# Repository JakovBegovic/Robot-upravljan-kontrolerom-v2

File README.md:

# Robot upravljan kontrolerom v2
[![CC BY-NC-SA 4.0][cc-by-nc-sa-shield]][cc-by-nc-sa]
<br>

Samostalan projekt studenta 2. godine diplomskog studija Jakova Begovića razvijen u svrhu učenja i razvijanja znanja. <br><br>
Koncipiran kao unaprjeđenje [projekta](https://github.com/JakovBegovic/Robot-upravljan-kontrolerom) razvijenog na 3. godini preddiplomskog studija. <br>
Uzima inspiraciju od prvotnog projekta i unaprjeđuje njegove značajke u svrhu povećane energetske učinkovitosti, korisničkog iskustva i funkcionalnosti.<br><br>

### Stanje razvoja dizajna za v2:
  - Razvijeni programski kodovi na prototipima električnih shema robot-auta i kontrolera ✅
  - Razvijene električne sheme robot-auta i kontrolera ✅
  - Dizajnirani PCB-i robot-auta i kontrolera ✅
  - Izrađeni PCB-i robot-auta i kontrolera ✅
  - Nabavljeni elektronički dijelovi robot-auta i kontrolera ✅
  - Razvijeni 2D modeli kućišta robot-auta i kontrolera ✅
  - Razvijeni 3D modeli kućišta robot-auta i kontrolera ❌
  - Isprintani 3D modeli kućišta robot-auta i kontrolera ❌
  - Elektronički dijelovi robot-auta i kontrolera povezani na PCB-ima ❌
  - Razvijeni programski kod prilagođen za sustave na PCB-ima ❌

<br>

### Korišteni alati:
  - KiCAD
    - razvoj električne sheme
    - dizajn PCB-a
      
  - LTSpice
    - simuliranje rada diskretnih sklopovskih komponenti
  
  - LibreCAD     
    - dizajn obruba PCB-a i 2D modela kućišta

  - VSC + PlatformIO
    - razvoj programskog koda

<br>

### Izjava o korištenju umjetne inteligencije: 

Umjetna inteligencija nije korištena za razvoj ovoga sustava, kao ni za istraživanje u svrhu istog. <br>
Istraživanje je provedeno koristeći knjige, Internetske izvore i nastavne materijale pohađanih fakulteta te kroz razgovor s radnicima u struci, s profesorima i s kolegama na fakultetima.
<br><br>
This work is licensed under a
[Creative Commons Attribution-NonCommercial-ShareAlike 4.0 International License][cc-by-nc-sa].

[![CC BY-NC-SA 4.0][cc-by-nc-sa-image]][cc-by-nc-sa]

[cc-by-nc-sa]: http://creativecommons.org/licenses/by-nc-sa/4.0/
[cc-by-nc-sa-image]: https://licensebuttons.net/l/by-nc-sa/4.0/88x31.png
[cc-by-nc-sa-shield]: https://img.shields.io/badge/License-CC%20BY--NC--SA%204.0-lightgrey.svg

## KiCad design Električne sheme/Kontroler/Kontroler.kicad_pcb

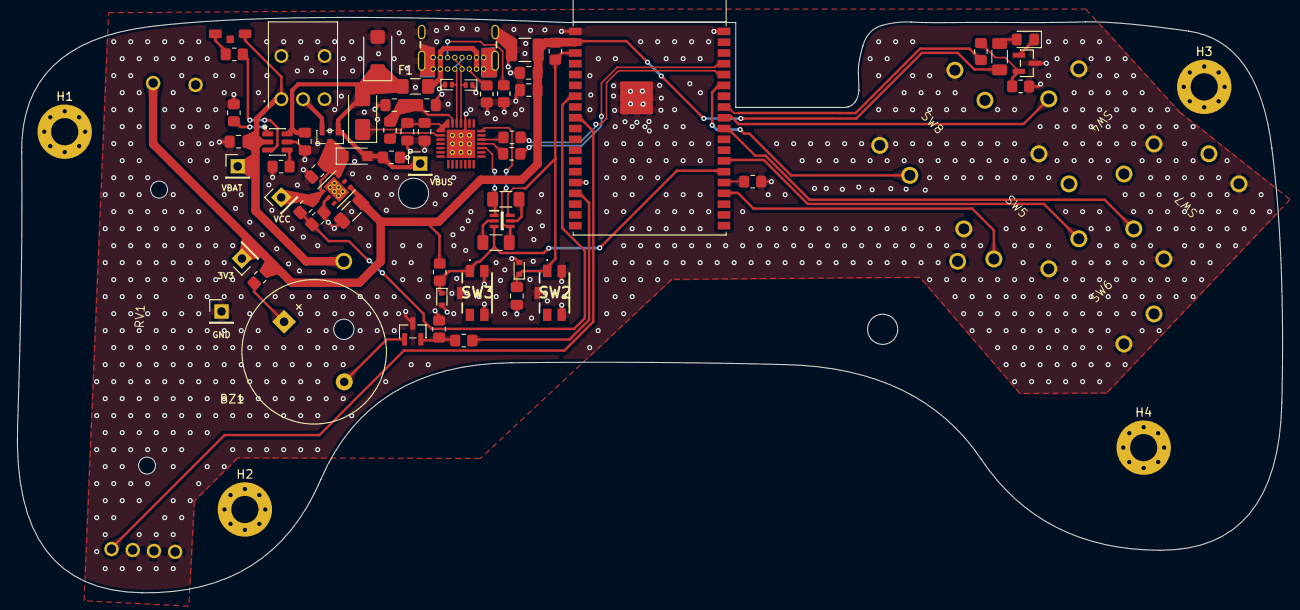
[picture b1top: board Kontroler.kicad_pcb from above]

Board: 2 copper layers, 148.9 x 67.7 mm, 73 parts (1 on the bottom side), 44 nets.

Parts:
BT1: 1S1P Li-Ion battery; 1043P
BZ1: Buzzer; LD-BZPN-1705
C1, C4, C5, C6, C7, C8, C11: 1u; C_0805_2012Metric_Pad1.18x1.45mm_HandSolder
C2, C3, C10: 100n; C_0805_2012Metric_Pad1.18x1.45mm_HandSolder
C9: 22u; C_1206_3216Metric_Pad1.33x1.80mm_HandSolder
C12: 10u; C_1210_3225Metric_Pad1.33x2.70mm_HandSolder
D2: PMEG3010BER; Nexperia_CFP3_SOD-123W
D3: STPS1L30A; D_SMA
D4: P4SMAJ5.0A; P25_DO-214AC_SMA
D5, D6: ESD5Z3V3; D_SOD-523
D7: LED_R_SMD; LED_0805_2012Metric_Pad1.15x1.40mm_HandSolder
D8: LED_B_SMD; LED_SMD_1204
D9, D17: STN101033B101; D_SOD-882D
F1: 1.2A quick acting; Fuse_1206_3216Metric_Pad1.42x1.75mm_HandSolder
H1, H2, H3, H4: MountingHole; MountingHole_3.2mm_M3_Pad_Via
J1: USB4920; GCT_USB4920-00-A_REVA
Q1: MMFTP3401; SOT-23_editable
Q2, Q3: 2N7002; SOT-23_editable
R1, R2: 5.1k; R_0805_2012Metric_Pad1.20x1.40mm_HandSolder_editable
R3: 100k; R_0805_2012Metric_Pad1.20x1.40mm_HandSolder_editable
R4: 4.7k; R_0805_2012Metric_Pad1.20x1.40mm_HandSolder
R5, R6: 470; R_0805_2012Metric_Pad1.20x1.40mm_HandSolder
R7: 1.2k; R_0805_2012Metric_Pad1.20x1.40mm_HandSolder
R8, R9, R14, R15, R17, R20: 10k; R_0805_2012Metric_Pad1.20x1.40mm_HandSolder_editable
R10, R13: 12k; R_1206_3216Metric_Pad1.30x1.75mm_HandSolder
R11, R12, R22: 1k; R_0805_2012Metric_Pad1.20x1.40mm_HandSolder_editable
R16, R19: 22; R_0805_2012Metric_Pad1.20x1.40mm_HandSolder_editable
R18: 62; R_1206_3216Metric_Pad1.30x1.75mm_HandSolder
R21: 3.9k; R_0805_2012Metric_Pad1.20x1.40mm_HandSolder_editable
RV1: RS45112A400G
SW1: 200MSP1T1B2M6QE
SW2, SW3: EVQP2F02K
SW4, SW5, SW6, SW7, SW8: TACTS-24K-F
TP1, TP2, TP3, TP4, TP5: TestPoint_Probe; PinHeader_1x01_P2.54mm_Vertical
U1: CP2102-GM; QFN50P500X500X100-29N-D
U2: BQ21040DBVR; SOT-23-6
U3: BC847BDW1T1G
U4: LD39100PU33R; DFN-6-editable
U5: ESP32-WROVER-E

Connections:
+3V3: C9.1, C10.1, C11.1, C12.1, R9.2, R14.1, R18.1, R21.1, RV1.3, TP3.1 (1_1), U4.4 (VOUT), U5.2 (3V3)
BZ: R19.1, U5.16 (MTCK/GPIO13/ADC2_CH4)
D+: D17.2 (A2), J1.A6 (D+), J1.B6 (D+), U1.4 (D+)
D-: D9.2 (A2), J1.A7 (D-), J1.B7 (D-), U1.5 (D-)
DTR: R10.2, U1.28 (DTR), U3.4 (E1)
EN: C7.1, D5.1 (K), R9.1, SW2.1, SW2.3, U3.6 (C2), U5.3 (EN/CHIP_PU)
GND: BT1.2 (-), C1.2, C2.2, C3.2, C4.2, C5.2, C6.2, C7.2, C8.2, C9.2, C10.2, C11.2, C12.2, D4.2 (A2), D5.2 (A), D6.2 (A), D9.1 (A1), D17.1 (A1), J1.A1 (GND), J1.A12 (GND), J1.B1 (GND), J1.B12 (GND), J1.SH1 (SHIELD), J1.SH2 (SHIELD), J1.SH3 (SHIELD), J1.SH4 (SHIELD), Q2.3 (S), Q3.3 (S), R1.1, R2.2, R3.2, R7.2, R8.1, R12.2, R15.1, R17.1, R20.2, RV1.2, RV1.4, RV1.5, RV1.6, SW1.3 (C), SW1.MH1, SW1.MH2, SW2.2, SW2.4, SW2.5 (GND_5), SW3.2, SW3.4, SW3.5 (GND_5), SW4.1, SW4.3, SW5.1, SW5.3, SW6.1, SW6.3, SW7.1, SW7.3, SW8.1, SW8.3, TP5.1 (1_1), U1.3 (GND_1), U1.29 (GND_2), U2.5 (GND), U4.2 (GND), U4.7 (GND), U5.1 (GND), U5.15 (GND), U5.38 (GND), U5.39 (GND_THERMAL)
IO0: D6.1 (K), R14.2, SW3.1, SW3.3, U3.3 (C1), U5.25 (GPIO0/BOOT/ADC2_CH1)
IO2: R15.2, U5.24 (ADC2_CH2/GPIO2)
LEDR: R16.2, U5.31 (GPIO19)
unnamed: BZ1.1 (+), R21.2
unnamed: BZ1.2 (-), Q3.1 (D)
unnamed: C3.1, C4.1, D3.1 (K), U1.7 (REGIN), U1.8 (VBUS)
unnamed: D7.2 (A), R18.2
unnamed: D7.1 (K), Q2.1 (D)
unnamed: D8.1 (K), R22.1
unnamed: F1.1, J1.A4 (VBUS), J1.A9 (VBUS), J1.B4 (VBUS), J1.B9 (VBUS)
unnamed: J1.A5 (CC1), R1.2
unnamed: J1.B5 (CC2), R2.1
unnamed: Q1.2 (S), SW1.2 (B)
unnamed: Q2.2 (G), R16.1, R17.2
unnamed: Q3.2 (G), R19.2, R20.1
unnamed: R6.2, U1.25 (RXD)
unnamed: R5.2, U1.26 (TXD)
unnamed: R4.1, U1.9 (~RST)
unnamed: R7.1, U2.4 (ISET)
unnamed: R8.2, U2.1 (TS)
unnamed: R13.2, U3.5 (B1)
unnamed: R10.1, U3.2 (B2)
RTS: R13.1, U1.24 (RTS), U3.1 (E2)
RV1: RV1.1, U5.9 (32K_XN/GPIO33/ADC1_CH5)
RX: R6.1, U5.35 (U0TXD/GPIO1)
SW1: SW4.2, SW4.4, U5.30 (GPIO18)
SW2: SW5.2, SW5.4, U5.23 (MTDO/GPIO15/ADC2_CH3)
SW3: SW6.2, SW6.4, U5.26 (ADC2_CH0/GPIO4)
SW4: SW7.2, SW7.4, U5.29 (GPIO5)
SW5: SW8.2, SW8.4, U5.33 (GPIO21)
TX: R5.1, U5.34 (U0RXD/GPIO3)
VBAT: BT1.1 (+), C6.1, D8.2 (A), SW1.1 (A), TP2.1 (1_1), U2.2 (OUT)
VBUS: C5.1, D2.2 (A), D3.2 (A), D4.1 (A1), F1.2, Q1.1 (G), R3.1, TP1.1 (1_1), U2.6 (VIN)
VCC: C8.1, D2.1 (K), Q1.3 (D), R11.1, TP4.1 (1_1), U4.1 (EN), U4.6 (VIN)
VCC_DVDD: R11.2, R12.1, U5.7 (GPIO35/ADC1_CH7)
VDD: C1.1, C2.1, R4.2, U1.6 (VDD)
~CHG: R22.2, U2.3 (~CHG)

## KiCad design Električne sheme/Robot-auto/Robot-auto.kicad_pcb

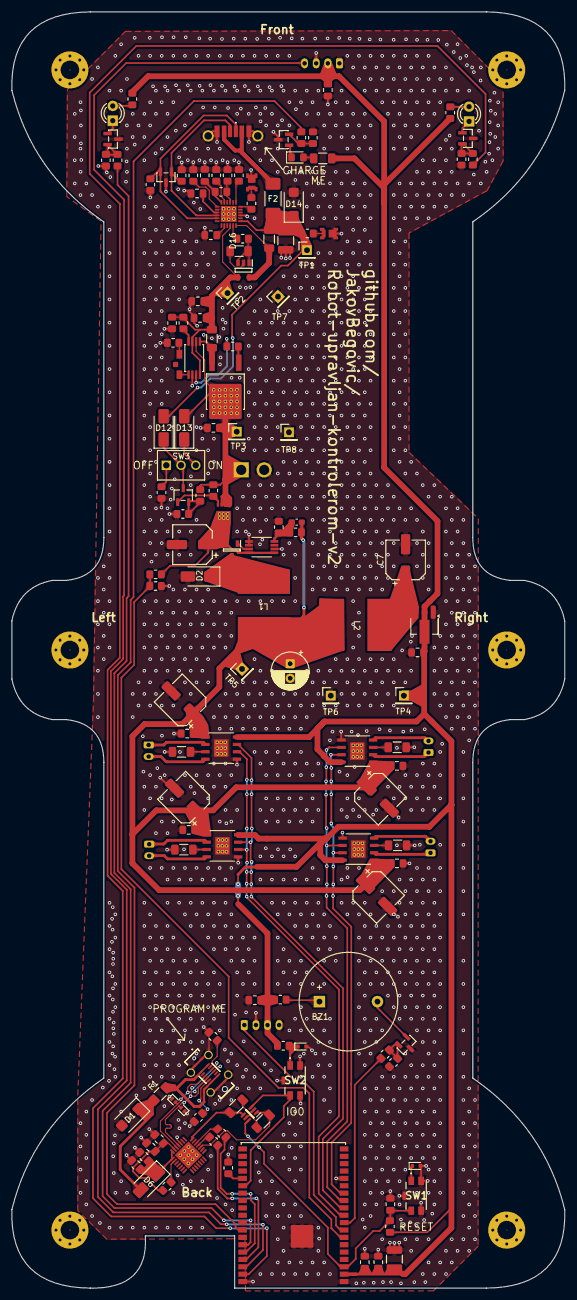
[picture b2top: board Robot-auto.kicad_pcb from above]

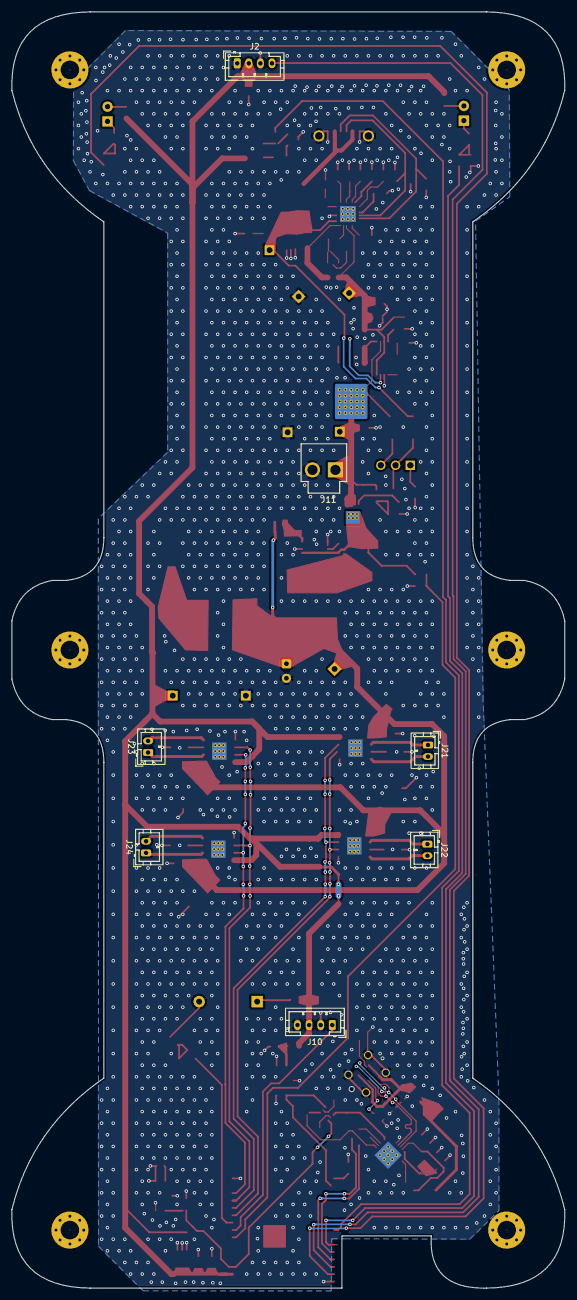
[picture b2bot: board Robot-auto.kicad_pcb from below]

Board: 2 copper layers, 95.3 x 220.0 mm, 149 parts (7 on the bottom side), 94 nets.

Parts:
BZ1: Buzzer; LD-BZPN-1705
C1: 33u; CP_Elec_6.3x7.7
C2: 120u; CP_Radial_D6.3mm_P2.50mm
C3, C10, C12, C16, C17, C18, C19, C21, C22, C23, C25, C27, C29: 100n; C_0805_2012Metric_Pad1.18x1.45mm_HandSolder
C4, C9, C11, C13, C15, C20: 1u; C_0805_2012Metric_Pad1.18x1.45mm_HandSolder
C5, C14: 10u; C_1210_3225Metric_Pad1.33x2.70mm_HandSolder
C6: 620p; C_0603_1608Metric_Pad1.08x0.95mm_HandSolder
C7, C24, C26, C28, C30: 47u; CP_Elec_6.3x7.7
C8: 22u; C_0805_2012Metric_Pad1.18x1.45mm_HandSolder
D1: P4SMAJ5.0A; P25_DO-214AC_SMA
D2: B320AE-13; D_SMA
D3, D17: STN101033B101; D_SOD-882D
D4, D5: ESD5Z3V3; D_SOD-523
D6, D12, D13: STPS1L30A; D_SMA
D7, D8: LED_Y_THT; LED_D3.0mm_Clear
D9: LED_R_SMD; LED_0805_2012Metric_Pad1.15x1.40mm_HandSolder
D10, D16: LED_G_SMD; N0G20S39
D11: LED_B_SMD; LED_SMD_1204
D14: P4SMAJ15A; P25_DO-214AC_SMA
D15: D5V0L2B3SO-7; SOT-23_editable
F1: 750 mA quick acting; Fuse_1206_3216Metric_Pad1.42x1.75mm_HandSolder
F2: 2A quick acting; 0679L2000-01_BEL-XL
H1, H2, H3, H4, H5, H6: MountingHole; MountingHole_3.2mm_M3_Pad_Via
J1: 16 pin USB-C receptacle; USB412003C
J2, J10: B4B-PH-K-S; JST_PH_B4B-PH-K_1x04_P2.00mm_Vertical
J6: Power-only 6-pin USB-C receptacle; USB4130GFC
J11: JST B2P-VH; JST_B2P-VH
J21, J22, J23, J24: B2B-PH-K-S; JST_PH_B2B-PH-K_1x02_P2.00mm_Vertical
L1: 100u; JNRH-1207-101M-A
L2: 22u; JNRH-1207-101M-A
Q1: DMP2045U; SOT23_3-pin
Q2, Q3, Q4, Q5: 2N7002; SOT-23_editable
Q6: MJD45H11T4G; TO229P990X238-3N
Q7: 2SC3326-A; S-MINI_TOS-M
R1: 30k; R_0805_2012Metric_Pad1.20x1.40mm_HandSolder
R2, R8, R40, R41: 5.1k; R_0805_2012Metric_Pad1.20x1.40mm_HandSolder_editable
R3, R4: 470; R_0805_2012Metric_Pad1.20x1.40mm_HandSolder
R5, R6: 12k; R_1206_3216Metric_Pad1.30x1.75mm_HandSolder
R7, R9, R10, R11, R21, R22, R23, R24, R28, R39, R42: 10k; R_0805_2012Metric_Pad1.20x1.40mm_HandSolder_editable
R12: 4.7k; R_0805_2012Metric_Pad1.20x1.40mm_HandSolder
R13: 3.9k; R_0805_2012Metric_Pad1.20x1.40mm_HandSolder_editable
R14, R15, R37: 100; R_0805_2012Metric_Pad1.20x1.40mm_HandSolder_editable
R16: 62; R_1206_3216Metric_Pad1.30x1.75mm_HandSolder
R17, R18, R19, R20: 22; R_0805_2012Metric_Pad1.20x1.40mm_HandSolder_editable
R25: 10m; R_1206_3216Metric_Pad1.30x1.75mm_HandSolder
R26: 82m; R_1206_3216Metric_Pad1.30x1.75mm_HandSolder
R27: 13k; R_0805_2012Metric_Pad1.20x1.40mm_HandSolder
R29, R32, R33, R35: 47k; R_0805_2012Metric_Pad1.20x1.40mm_HandSolder_editable
R30: 7.5k; R_0805_2012Metric_Pad1.20x1.40mm_HandSolder
R31, R38: 1k; R_0805_2012Metric_Pad1.20x1.40mm_HandSolder_editable
R34: 10M; R_1206_3216Metric_Pad1.30x1.75mm_HandSolder
R36: 33k; R_0805_2012Metric_Pad1.20x1.40mm_HandSolder
R43: 16k; R_0805_2012Metric_Pad1.20x1.40mm_HandSolder_editable
R44: 0; R_0805_2012Metric_Pad1.20x1.40mm_HandSolder_editable
R45, R46, R47: 100k; R_0805_2012Metric_Pad1.20x1.40mm_HandSolder_editable
R48, R49, R50, R51: 330m; R_1206_3216Metric_Pad1.30x1.75mm_HandSolder
SW1, SW2: EVQP2F02K
SW3: 200MSP1T2B4M2QE; SW_200MSP1T2B4M2QE
TP1, TP2, TP3, TP4, TP5, TP6, TP7, TP8: TestPoint_Probe; PinHeader_1x01_P2.54mm_Vertical
U1: BC847BDW1T1G
U2: LM3485
U3: LDI1117-3.3U; SOT-89-3_Handsoldering
U4: ESP32-WROVER-E
U5: CP2102-GM; QFN50P500X500X100-29N-D
U6: WMQ50P03T1; PDFN3030-8L
U8: BQ2057WTS; TSSOP-8_4.4x3mm_P0.65mm_editable
U9: QS5K2TR; SOT95P280X100-5N
U11: AP33771DKZ-13; W-QFN4040-24_ThermalVias
U12, U13, U14, U15: DRV8251DDAR; POWERPAD_DDA_TEX

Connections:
+3V3: C3.1, C4.1, C5.1, C8.1, C17.1, C19.1, J2.2, J10.3, R7.1, R11.2, R13.1, R14.1, R15.1, R16.1, TP4.1 (1_1), U3.2 (VOUT), U4.2 (3V3), U12.4 (VREF), U13.4 (VREF), U14.4 (VREF), U15.4 (VREF)
+3V3PD: C22.1, R44.2, U11.12 (V3VD)
+5V: C2.1, C6.1, C23.2, C24.1, C25.2, C26.1, C27.2, C28.1, C29.2, C30.1, L1.2, L2.1, R1.2, TP5.1 (1_1), U12.5 (VM), U13.5 (VM), U14.5 (VM), U15.5 (VM)
BZ: R20.1, U4.9 (32K_XN/GPIO33/ADC1_CH5)
CC1: D15.2 (A2), J6.A5 (CC1), R40.2, U11.17 (CC1)
CC2: D15.1 (A1), J6.B5 (CC2), R41.2, U11.16 (CC2)
D+: D17.2 (A2), J1.A6 (D+), J1.B6 (D+), U5.4 (D+)
D-: D3.2 (A2), J1.A7 (D-), J1.B7 (D-), U5.5 (D-)
DIST1: J2.4, U4.36 (GPIO22)
DIST2: J10.1, U4.8 (32K_XP/GPIO32/ADC1_CH4)
DTR: R5.2, U1.4 (E1), U5.28 (DTR)
EN: C11.1, D4.1 (K), R11.1, SW1.1, SW1.3, U1.6 (C2), U4.3 (EN/CHIP_PU)
GND: C1.2, C2.2, C3.2, C4.2, C5.2, C7.2, C8.2, C9.2, C10.2, C11.2, C12.2, C13.2, C14.2, C15.2, C16.2, C17.2, C18.2, C19.2, C20.2, C21.2, C22.2, C23.1, C24.2, C25.1, C26.2, C27.1, C28.2, C29.1, C30.2, D1.2 (A2), D2.2 (A), D3.1 (A1), D4.2 (A), D5.2 (A), D10.1 (K), D14.2 (A2), D15.3 (common), D16.1 (K), D17.1 (A1), J1.A1 (GND), J1.A12 (GND), J1.B1 (GND), J1.B12 (GND), J1.SH (SHIELD), J2.1, J2.3, J6.A12 (GND), J6.B12 (GND), J6.MH1 (SHIELD), J6.MH2 (SHIELD), J10.2, J10.4, J11.2, Q2.3 (S), Q3.3 (S), Q4.3 (S), Q5.3 (S), R2.1, R8.2, R9.1, R10.2, R21.2, R22.2, R23.1, R24.2, R30.1, R35.1, R36.2, R38.2, R39.2, R40.1, R41.1, R43.1, R45.2, R46.2, R47.2, R48.2, R49.2, R50.2, R51.2, SW1.2, SW1.4, SW1.5 (GND_5), SW2.2, SW2.4, SW2.5 (GND_5), TP6.1 (1_1), TP7.1 (1_1), TP8.1 (1_1), U2.2 (GND), U2.5 (ADJ), U2.6 (PWR_GND), U3.1 (GND), U4.1 (GND), U4.15 (GND), U4.38 (GND), U4.39 (GND_THERMAL), U5.3 (GND_1), U5.29 (GND_2), U8.6 (VSS), U11.3 (GND), U11.25 (EP), U12.1 (GND), U12.9 (EP), U13.1 (GND), U13.9 (EP), U14.1 (GND), U14.9 (EP), U15.1 (GND), U15.9 (EP)
IN1A: U4.11 (DAC_2/ADC2_CH9/GPIO26), U12.3 (IN1), U13.3 (IN1)
IN1B: U4.13 (MTMS/GPIO14/ADC2_CH6), U14.3 (IN1), U15.3 (IN1)
IN1M1: J21.1, U12.6 (OUT1)
IN1M2: J23.1, U14.6 (OUT1)
IN1M3: J22.1, U13.6 (OUT1)
IN1M4: J24.1, U15.6 (OUT1)
IN2A: U4.10 (DAC_1/ADC2_CH8/GPIO25), U12.2 (IN2), U13.2 (IN2)
IN2B: U4.12 (ADC2_CH7/GPIO27), U14.2 (IN2), U15.2 (IN2)
IN2M1: J21.2, U12.8 (OUT2)
IN2M2: J23.2, U14.8 (OUT2)
IN2M3: J22.2, U13.8 (OUT2)
IN2M4: J24.2, U15.8 (OUT2)
IO0: D5.1 (K), R7.2, SW2.1, SW2.3, U1.3 (C1), U4.25 (GPIO0/BOOT/ADC2_CH1)
IO2: R9.2, U4.24 (ADC2_CH2/GPIO2)
LED1: R17.1, U4.33 (GPIO21)
LED2: R18.1, U4.37 (GPIO23)
LED3: R19.2, U4.31 (GPIO19)
unnamed: BZ1.1 (+), R13.2
unnamed: BZ1.2 (-), Q5.1 (D)
unnamed: D2.1 (K), L1.1, Q1.3 (D)
unnamed: C12.1, C13.1, D6.1 (K), U5.7 (REGIN), U5.8 (VBUS)
unnamed: D7.2 (A), R14.2
unnamed: D7.1 (K), Q2.1 (D)
unnamed: D8.2 (A), R15.2
unnamed: D8.1 (K), Q3.1 (D)
unnamed: D9.2 (A), R16.2
unnamed: D9.1 (K), Q4.1 (D)
unnamed: D10.2 (A), R28.2
unnamed: D11.2 (A), U8.5 (STAT)
unnamed: D11.1 (K), R38.1
unnamed: D12.1 (K), Q7.3 (E), SW3.2 (B)
unnamed: D13.1 (K), SW3.3 (C)
unnamed: D16.2 (A), R42.1
unnamed: F1.1, J1.A4 (VBUS), J1.A9 (VBUS), J1.B4 (VBUS), J1.B9 (VBUS)
unnamed: F2.1, J6.A9 (VBUS), J6.B9 (VBUS)
unnamed: J1.A5 (CC1), R2.2
unnamed: J1.B5 (CC2), R8.1
unnamed: Q1.1 (G), U2.7 (PGATE)
unnamed: Q2.2 (G), R17.2, R21.1
unnamed: Q3.2 (G), R18.2, R22.1
unnamed: Q4.2 (G), R19.1, R23.2
unnamed: Q5.2 (G), R20.2, R24.1
unnamed: Q6.1 (B), R31.1
unnamed: Q6.3 (E), R26.2, U8.1 (SNS)
unnamed: Q7.2 (B), R32.2, R36.1
unnamed: Q7.1 (C), R29.1, U6.4 (G)
unnamed: R39.1, SW3.1 (A)
unnamed: R6.2, U1.5 (B1)
unnamed: R5.1, U1.2 (B2)
unnamed: C6.2, R1.1, R10.1, U2.4 (FB)
unnamed: C7.1, L2.2, U3.3 (VIN)
unnamed: R4.2, U5.25 (RXD)
unnamed: R3.2, U5.26 (TXD)
unnamed: R12.1, U5.9 (~RST)
unnamed: R31.2, U8.7 (CC)
unnamed: R33.1, U8.4 (TS)
unnamed: R34.1, R37.2, U9.1 (G1), U9.3 (G2)
unnamed: R34.2, U9.2 (S)
unnamed: R42.2, U11.6 (GPIO4)
unnamed: C21.1, U11.15 (IFB)
unnamed: R43.2, U11.13 (PSEL)
unnamed: R37.1, U11.23 (PWR_EN)
unnamed: C20.1, U11.20 (V5V)
unnamed: R25.2, U9.5 (D1), U11.24 (VCC)
unnamed: R44.1, R46.1, U11.9 (VSEL0)
unnamed: R45.1, U11.7 (VSEL1)
unnamed: R47.1, U11.11 (VSEL2)
unnamed: R48.1, U12.7 (ISEN)
unnamed: R49.1, U13.7 (ISEN)
unnamed: R50.1, U14.7 (ISEN)
unnamed: R51.1, U15.7 (ISEN)
RTS: R6.1, U1.1 (E2), U5.24 (RTS)
RX: R4.1, U4.35 (U0TXD/GPIO1)
TX: R3.1, U4.34 (U0RXD/GPIO3)
VBAT: C16.1, D13.2 (A), J11.1, Q6.4 (C), R29.2, R32.1, TP3.1 (1_1), U6.1 (S), U6.2 (S), U6.3 (S), U8.2 (BAT)
VBUS1: C14.1, D12.2 (A), D14.1 (A1), F2.2, R25.1, R28.1, TP1.1 (1_1), U11.1 (ISENP)
VBUS2: D1.1 (A1), D6.2 (A), F1.2
VCC: C1.1, Q1.2 (S), R27.1, U2.1 (ISENSE), U2.8 (VIN), U6.5 (D)
VCC_DVDD: R27.2, R30.2, U4.7 (GPIO35/ADC1_CH7)
VCHRG: C15.1, C18.1, R26.1, R33.2, R35.2, TP2.1 (1_1), U8.3 (VCC), U8.8 (COMP), U9.4 (D2), U11.22 (VBUS)
VDD: C9.1, C10.1, R12.2, U5.6 (VDD)

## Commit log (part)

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2025-11-19 Inicijalizirao novi repozitorij s 2 PlatformIO projekta.
2025-11-19 Proširio platformio.ini datoteke kako bi radile sa serijskom komunikacijom putem USB priključka.
2025-11-19 Povezao serijsku komunikaciju s gumbovima na protopločici.
2025-11-20 Kopirao kod iz robotove u kontrolersku datoteku.
2025-11-20 Omogućio uključivanje i gašenje LED diode.
2025-11-20 Omogućio cikličko paljenje 5 LE dioda.
2025-11-20 Zapisao MAC adrese mikroupravljača kontrolera i robot-auta.
2025-11-20 Omogućio ESP NOW komunikaciju između kontrolera i robot-auta.
2025-11-21 Promijenio tipove podataka koji se koriste za upravljanje IO pinovima iz int u uint8_t.
2025-11-23 Promijenio varijablu koja upravlja vremenom slanja iz lokalne u globalnu.
2025-11-23 Promijenio varijablu koja sadrži podatke o primatelju poruka iz globalne u lokalnu.
2025-11-23 Promijenio grupaciju globalnih varijabli.
2025-11-23 Logiku slanja poruka učahurio u funkciju.
2025-11-23 Omogućio provjeru ispravnog slanja poruke.
2025-11-23 Omogućio slanje paketa samo na promjenu poruke.
2025-11-23 Učahurio logiku upravljanja LED-icama u zasebnu funkciju.
2025-11-23 Promijenio grupaciju naredbi u setup() funkciji.
2025-11-23 Promijenio imena varijabli u svrhu čitkosti koda.
2025-11-28 Pomaknuo programski kod u zasebnu datoteku.
2025-11-28 Preimenovao datoteku koja sadrži programski kod.
2025-11-28 Izradio novi KiCad projekt koji opisuje električnu shemu kontrolera.
2025-11-30 Dodao datoteku električne sheme kontrolera.
2025-11-30 Napravio novi KiCad projekt za električnu shemu robot auta.
2025-11-30 Nacrtao električnu šemu za robot-auto.
2025-12-01 U šemu dodao prekidač za gašenje i paljenje mikroupravljača kontrolera.
    Ulazni pin RESET razvojne pločice se povezuje na ulazni pin EN mikroupravljača. Mikroupravljač je omogućen za EN = HIGH.
2025-12-01 U šemu dodao prekidač za gašenje i paljenje mikroupravljača robot-auta.
    Ulazni pin RESET razvojne pločice se povezuje na ulazni pin EN mikroupravljača. Mikroupravljač je omogućen za EN = HIGH.
2025-12-02 Refaktorirao programski kod kontrolera.
2025-12-02 Omogućio postavljanje LED-ica na zadanu vrijednost 0 u slučaju da niti jedna poruka nije dobivena unutar posljednjih 750 milisekundi.
2025-12-02 Dodao enumerator za vrijednosti dobivene od kontrolera.
2025-12-02 Dodao enumerator za vrijednosti slane robot-autu.
2025-12-02 Omogućio automatsko slanje poruke svakih 500 milisekundi kako ne bi došlo do zaustavljanja robot-auta.
2025-12-02 Dodao uvjet da se ne mora slati zadana vrijednost robot-auta.
    Napisano u svrhu smanjenja broja poruka i samim time potrošene energije.
2025-12-02 Refaktorirao kod robot-auta.
2025-12-03 Izbjegao okidanje watchdog timera na neuspješno slanje paketa i iskoristio ACK poruku koja je slana od primatelja za potvrdu uspješno poslanog paketa.
2025-12-03 Dodao logiku povećavanja vremena između poslanih poruka ukoliko je došlo do 10 neuspjelih.
    Korist je umanjenje potrošnje baterije ukoliko ne postoji veza između kontrolera i robot-auta.
2025-12-03 Izmijenio tipove varijabli kako bi odgovarale ostatku programskog koda.
2025-12-03 Dodao potenciometar u električnu shemu kontrolera.
2025-12-03 Uredio električnu šemu robot-auta.
2025-12-03 Izveo čitanje stanja upravljačke elektronike u posebnu funkciju.
2025-12-03 Uredio uvjete za slanje poruke.
    Grupirao if i if else izraze u jedan if izraz s granatim uvjetima.
2025-12-10 Obrisao backup direktorije za kontroler i robot-auto.
2025-12-12 Obogatio podatke slane putem antene.
    Omogućio slanje naredbi o pomicanju naprijed-natrag, rotacije lijevo-desno i brzine kretanja.
2025-12-15 Obrisao nekorištene varijable u programskom kodu robot-auta.
2025-12-15 Dodao makro za uključivanje i isključivanje poruka putem serijske komunikacije.
2025-12-15 Onemogućio slanje paketa prije nego što korisnik pritisne gumb. Izmijenio tip pripisivanja vrijednosti prijašnje i sadašnje poruke.
    Pretpostavlja se da je nulti paket primljen jer su zadane vrijednosti tog paketa već zapisane u programskom kodu robot-auta.
2025-12-15 Umanjio vrijeme čekanja paketa do postavljanja zadanih vrijednosti.
2025-12-15 Osigurao postavljanje zadanih vrijednosti na izlaze mikroupravljača robot-auta.
2025-12-15 Izuzeo ispit uvjeta za slanje paketa iz funkcije sendMessage() i isti uklopio u if naredbu unutar loop() funkcije.
2025-12-15 Izuzeo logiku nošenja s neprimljenim porukama iz funkcije onDataSent() u if naredbu unutar loop() funkcije.
2025-12-15 Uredio format programskog koda if uvjeta loop() funkcije robot-auta.
2025-12-15 Omogućio očitanje vrijednosti brzine kretanja robot-auta s potenciometra na kontroleru.
    Dodao maržu greške između dva očitanja promjene vrijednosti na +- 200.
2025-12-15 Promijenio šemu kontrolera kako bi pravilno prikazivala broj pina na koji je spojen potenciometar.
2025-12-15 Privremene lokalne datoteke dodao u .gitignore.
    Datoteke koje KiCAD koristi kada se uređuje jedna od šema.
2025-12-16 Dodao klasu HardwareReader koja upravlja čitanjem podataka s korisničkog unosa na pločici.
2025-12-16 Promijenio poredak metoda u datoteci HardwareReader.cpp.
2025-12-16 Uredio dokumentaciju klase HardwareReader.
2025-12-16 Kreirao klasu MessageSender koja upravlja slanjem poruka putem ESP NOW protokola. Odvojio definiciju sloga i operator != nad slogom u posebnu zaglavnu datoteku.
2025-12-16 Dodao kod za debugiranje putem serijskog monitora.
2025-12-16 Preimenovao klasu MessageSender u CommsController.
2025-12-16 Varijablu failedMsgsInARow premjestio u klasu.
2025-12-17 Preimenovao funkciju onDataSent u dataSentCb.
2025-12-17 Funkciju constructMsg pretvorio u metodu klase CommsController.
2025-12-17 Varijable messageToSend i lastMessageSent premjestio u klasu CommsController.
2025-12-17 Provjeru uvjeta za slanje poruke pretvorio u metodu klase CommsController.
2025-12-17 Uvjete za slanje poruke preko ESP NOW protokola odvojio u zasebne metode.
2025-12-17 Promijenio definiciju metode sendMessage kako bi radila s varijablom klase CommsController. Promijenio ime metode sendMessage u sendConstructedMessage.
2025-12-17 Pohranu zadnje uspješno primljene poruke premjestio u metodu sendConstructedMessage.
2025-12-17 Dodao opis metode sendConstructedMessage.
2025-12-17 Varijable lastTimeMsgSent i lastMessageSent pretvorio u privatne.
2025-12-17 Definirao metodu confirmSuccessfulSend za provođene logike o uspješnom slanju poruke.
2025-12-17 Dodao opis metode constructMsg.
2025-12-17 Premjestio mjesto deklaracije varijable result u main.cpp datoteci.
2025-12-17 Promijenio ime metode sendConstructedMessage u sendConstructedMsg.
2025-12-17 Promijenio naziv funkcije onDataSent u dataRecievedInfo.
2025-12-17 Dodao getter za varijablu constructedMsg.
2025-12-17 Klasu HardwareReader pretvorio u namespace.
2025-12-17 Privatne funkcije namespacea HardwareReader premjestio u .h datoteku.
2025-12-17 Obrisao nekorištenu include direktivu.
2025-12-17 Neimenovani namespace prebačen iz zaglavne u .cpp datoteku.
    Pogledaj C++ Core Guidelines SF21 i SF22.
2025-12-17 Promijenio opis HardwareReader namespacea.
2025-12-17 Klasu CommsController pretvorio u namespace.
2025-12-17 Datoteke MsgStruct preimenovao u msgStruct.
2025-12-17 Callback funkciju koja obrađuje potvrdnu poruku o dobivenom paketu premjestio iz main.cpp u CommsController namespace.
2025-12-17 Doradio komentare u neimenovanim namespaceovima unutar CommsController.cpp i HardwareReader.cpp.
2025-12-18 Dodao komentare koji opisuju arhitekturu .h i .cpp datoteka koje sadrže namespaceove.
2025-12-18 Zadane vrijendosti poruke postavio u CommsController::setup() funkciji umjesto u samom msgStruct.
2025-12-18 Promijenio mjesto deklaracije funkcije confirmSuccessfulSend().
2025-12-18 Kreirao funkciju copyMsg() za kopiranje iz jedne u drugu msgStruct.
2025-12-18 Doradio uvjet za slanje poruke ažuriranja.
    Onemogućio slanje iste na promjenu vrijednosti speed ukoliko su vrijednosti moveDirection i rotation 0.
2025-12-18 Uvjet provjere poklapanja naredbe za brzinom izveo u zasebnu funkciju.
2025-12-18 Promijenio identaciju kod grananja uvjeta.
2025-12-21 Programski kod robot-auta razdijelio u namespaceove CommsController i HrdwrController. Slog msgStruct definirao u posebnoj zaglavnoj datoteci.
2025-12-21 Dodao opise funkcija dodanih namespaceova.
2025-12-21 Promijenio definiciju funkcije controlLEDs namespacea HrdwrController.
2025-12-21 Dodao datoteku tehnička uputstva u .gitignore.
2025-12-22 Definirao električnu shemu robot-auta.
2025-12-22 Dodao motore u električnu shemu robot-auta.
2025-12-22 Doradio pozicije električnih komponenti u shemi.
2025-12-22 Doradio električnu shemu kontrolera.
    Dodao zujalicu i bateriju.
2025-12-22 Grupirao dijelove sheme. Dodao ulaz za čitanje naponske razine baterije.
2025-12-22 Dodao indikatore za punjenje.
2025-12-22 Na šemi robot-auta dodao prekidač za uklapanje i isklapanje napajanja i oduzeo jedan naponski izvor iz šeme.
2025-12-22 Shemama dodao verziju.
2025-12-22 Promijenio pin-ove LE-dioda kako bi odgovarali onima na novo električnoj shemi. Omogućio upravljanje MTR_EN pinom putem MCPWM biblioteke. Omogućio slanje signala koji odgovaraju upravljačkim signalim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
2025-12-23 Reformatirao kod kako bi unaprijedio arhitekturu sustava.
2025-12-24 Omogućio izvođenje pjesme pomoću posebnog taska na jezgri 1.
2025-12-25 Omogućio izvedbu pjesme na zujalicu s odabirom pjesme promjenom varijable songPlaying.
2025-12-25 Omogućio promjenu izvođene pjesme pomoću poruke preko queuea.
2025-12-25 Omogućio promjenu izvođene pjesme na pritisak gumba.
2025-12-25 Promijenio ime namespacea HardwareReader u HrdwrReader.
2025-12-25 Omogućio pokretanje muzike samo nakon prvog pritiska gumba.
2025-12-26 Omogućio pritisak gumba za izvođenje sljedeće pjesme i držanje gumba za zastavljanje muzike.
2025-12-26 Funkciju za upravljanje pokretanja zujalice premjestio iz HrdwrReader u HrdwrController.
2025-12-26 Funkciju playSong pretvorio u privatnu i dodao posebnu setup funkciju za postavljanje iste.
2025-12-27 Dodao melodiju iz Super Mario igrica.
2025-12-27 Omogućio izvedbu više drugačijih pjesama.
    Izvođena pjesma se može promijeniti pritiskom na gumb na kontroleru. Izvođenje pjesme se može zaustaviti dugim pritiskom gumba na kontroleru.
2025-12-27 Omogućio nastavak izvedbe muzike umjesto preskakanja pjesme nakon što je pjesma prestala biti pauzirana.
2025-12-27 Pretvorio određene funkcije namespacea HrdwrController u privatne.
2025-12-27 Dodao posebnu funkciju za ispitivanje je li muzika pauzirana.
2026-01-02 Dodao opis funkcije readMusicBtn namespacea HrdwrReader.
2026-01-02 Dodao varijablu koja sadrži minimalno virjeme između slanja 2 poruke putem ESP NOW protokola. Koristio tu varijablu za izračunavanje vremenga odgode glavnog taska.
2026-01-02 Pomaknuo Serial.println() naredbe.
2026-01-03 Prioritete taskova zadao kao const varijable.
2026-01-04 Preimenovao funkcije koje sadrže logiku taskova kako bi sadržavale riječ task.
2026-01-04 Naredbe kreiranja taskova preselio u namespace Tasker.
2026-01-04 Dodao include direktivu za Tasker header.
2026-01-04 Izmijenio el. šemu kontrolera kako bi odgovarala programskom kodu.
2026-01-09 Obrisao nepotrebne komentare i include direktive.
2026-02-03 Ažurirao KiCAD verziju na 9.0. Promijenio imena motora u shemi.
2026-03-15 Ažurirao gitignore.
2026-03-15 Kreirao novi task za očitanje podataka s ADC-a.
2026-03-15 Dizajnirao naponsko djelilo za ulaz u ADC za mjerenje napona iz baterije.
2026-03-15 Napisao funkciju postavljanja gušenja.
2026-03-24 Dodao posebnu varijablu za definiciju gušenja kod pina na kojem se mjeri napon baterije.
2026-03-24 Napisao jednadžbu za promjenu vrijednosti koju ADC izmjeri u napon na VBAT čvoru. Doradio iznose otpornika u naponskom djelilu.
2026-03-24 Dodao pojašnjenje za izvor vrijednosti konstante za promjenu LSB-a u napon.
2026-03-24 Logiku za upravljanje aktuatorima za signaliranje razine napunjenosti korisniku prebačena u HrdwrController namespace.
2026-03-24 Dodao NMOS-ove za upravljanje LE-diodama i zujalicom.
